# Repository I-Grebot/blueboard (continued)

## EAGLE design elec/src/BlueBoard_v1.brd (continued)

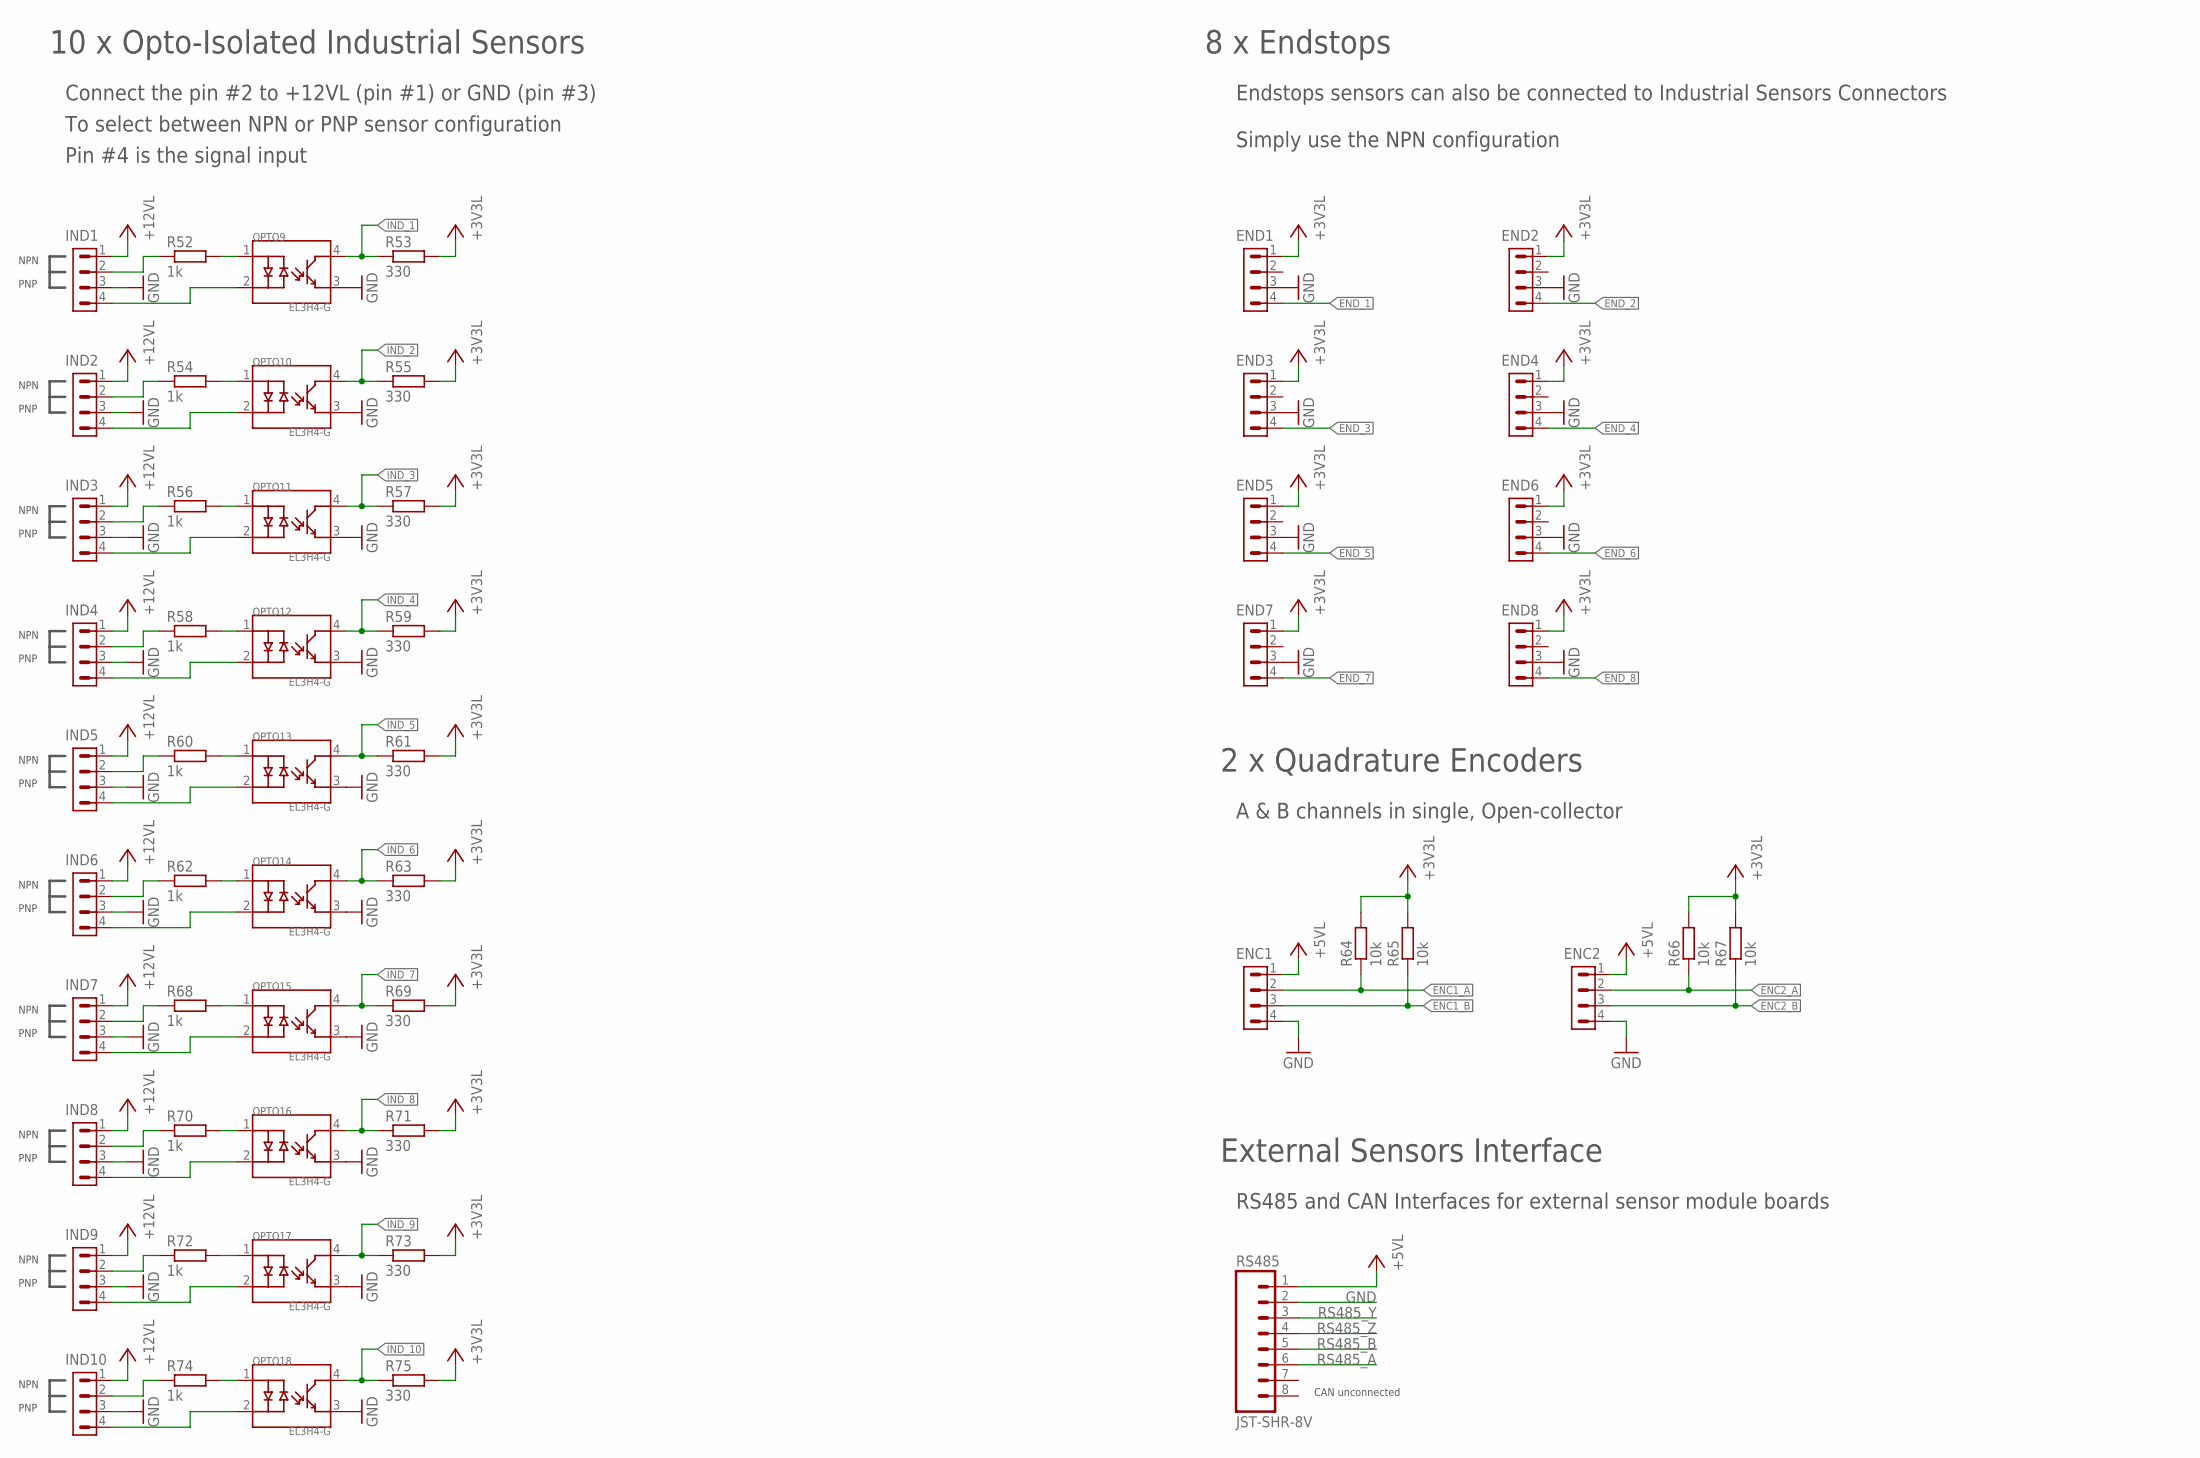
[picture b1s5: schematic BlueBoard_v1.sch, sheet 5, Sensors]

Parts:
ENC1, ENC2: CON_1.27_4
END1, END2, END3, END4, END5, END6, END7, END8: CON_1.27_4
IND1, IND2, IND3, IND4, IND5, IND6, IND7, IND8, IND9, IND10: CON_1.27_4
OPTO9, OPTO10, OPTO11, OPTO12, OPTO13, OPTO14, OPTO15, OPTO16, OPTO17, OPTO18: EL3H4-G; SSOP_4
R52, R54, R56, R58, R60, R62, R68, R70, R72, R74: 1k; R0603
R53, R55, R57, R59, R61, R63, R69, R71, R73, R75: 330; R0603
R64, R65, R66, R67: 10k; R0603
RS485: JST-SHR-8V; JST-SHR-08V

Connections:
+3V3L: END1.1, END2.1, END3.1, END4.1, END5.1, END6.1, END7.1, END8.1, R53.2, R55.2, R57.2, R59.2, R61.2, R63.2, R64.2, R65.2, R66.2, R67.2, R69.2, R71.2, R73.2, R75.2; also elsewhere on the board
+5VL: ENC1.1, ENC2.1, RS485.1; also elsewhere on the board
+12VL: IND1.1, IND2.1, IND3.1, IND4.1, IND5.1, IND6.1, IND7.1, IND8.1, IND9.1, IND10.1; also elsewhere on the board
ENC1_A: ENC1.2, R64.1; also elsewhere on the board
ENC1_B: ENC1.3, R65.1; also elsewhere on the board
ENC2_A: ENC2.2, R66.1; also elsewhere on the board
ENC2_B: ENC2.3, R67.1; also elsewhere on the board
END_1: END1.4; also elsewhere on the board
END_2: END2.4; also elsewhere on the board
END_3: END3.4; also elsewhere on the board
END_4: END4.4; also elsewhere on the board
END_5: END5.4; also elsewhere on the board
END_6: END6.4; also elsewhere on the board
END_7: END7.4; also elsewhere on the board
END_8: END8.4; also elsewhere on the board
GND: ENC1.4, ENC2.4, END1.3, END2.3, END3.3, END4.3, END5.3, END6.3, END7.3, END8.3, IND1.3, IND2.3, IND3.3, IND4.3, IND5.3, IND6.3, IND7.3, IND8.3, IND9.3, IND10.3, OPTO9.3, OPTO10.3, OPTO11.3, OPTO12.3, OPTO13.3, OPTO14.3, OPTO15.3, OPTO16.3, OPTO17.3, OPTO18.3, RS485.2; also elsewhere on the board
IND_1: OPTO9.4, R53.1; also elsewhere on the board
IND_2: OPTO10.4, R55.1; also elsewhere on the board
IND_3: OPTO11.4, R57.1; also elsewhere on the board
IND_4: OPTO12.4, R59.1; also elsewhere on the board
IND_5: OPTO13.4, R61.1; also elsewhere on the board
IND_6: OPTO14.4, R63.1; also elsewhere on the board
IND_7: OPTO15.4, R69.1; also elsewhere on the board
IND_8: OPTO16.4, R71.1; also elsewhere on the board
IND_9: OPTO17.4, R73.1; also elsewhere on the board
IND_10: OPTO18.4, R75.1; also elsewhere on the board
unnamed: IND1.2, R52.1
unnamed: OPTO9.1, R52.2
unnamed: IND1.4, OPTO9.2
unnamed: IND2.2, R54.1
unnamed: OPTO10.1, R54.2
unnamed: IND2.4, OPTO10.2
unnamed: IND3.2, R56.1
unnamed: OPTO11.1, R56.2
unnamed: IND3.4, OPTO11.2
unnamed: IND4.2, R58.1
unnamed: OPTO12.1, R58.2
unnamed: IND4.4, OPTO12.2
unnamed: IND5.2, R60.1
unnamed: OPTO13.1, R60.2
unnamed: IND5.4, OPTO13.2
unnamed: IND6.2, R62.1
unnamed: OPTO14.1, R62.2
unnamed: IND6.4, OPTO14.2
unnamed: IND7.2, R68.1
unnamed: OPTO15.1, R68.2
unnamed: IND7.4, OPTO15.2
unnamed: IND8.2, R70.1
unnamed: OPTO16.1, R70.2
unnamed: IND8.4, OPTO16.2
unnamed: IND9.2, R72.1
unnamed: OPTO17.1, R72.2
unnamed: IND9.4, OPTO17.2
unnamed: IND10.2, R74.1
unnamed: OPTO18.1, R74.2
unnamed: IND10.4, OPTO18.2
RS485_A: RS485.6; also elsewhere on the board
RS485_B: RS485.5; also elsewhere on the board
RS485_Y: RS485.3; also elsewhere on the board
RS485_Z: RS485.4; also elsewhere on the board

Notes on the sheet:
10 x Opto-Isolated Industrial Sensors
8 x Endstops
NPN
PNP
Connect the pin #2 to +12VL (pin #1) or GND (pin #3)
To select between NPN or PNP sensor configuration
Endstops sensors can also be connected to Industrial Sensors Connectors
Simply use the NPN configuration
External Sensors Interface
RS485 and CAN Interfaces for external sensor module boards
Pin #4 is the signal input
2 x Quadrature Encoders
A & B channels in single, Open-collector
CAN unconnected

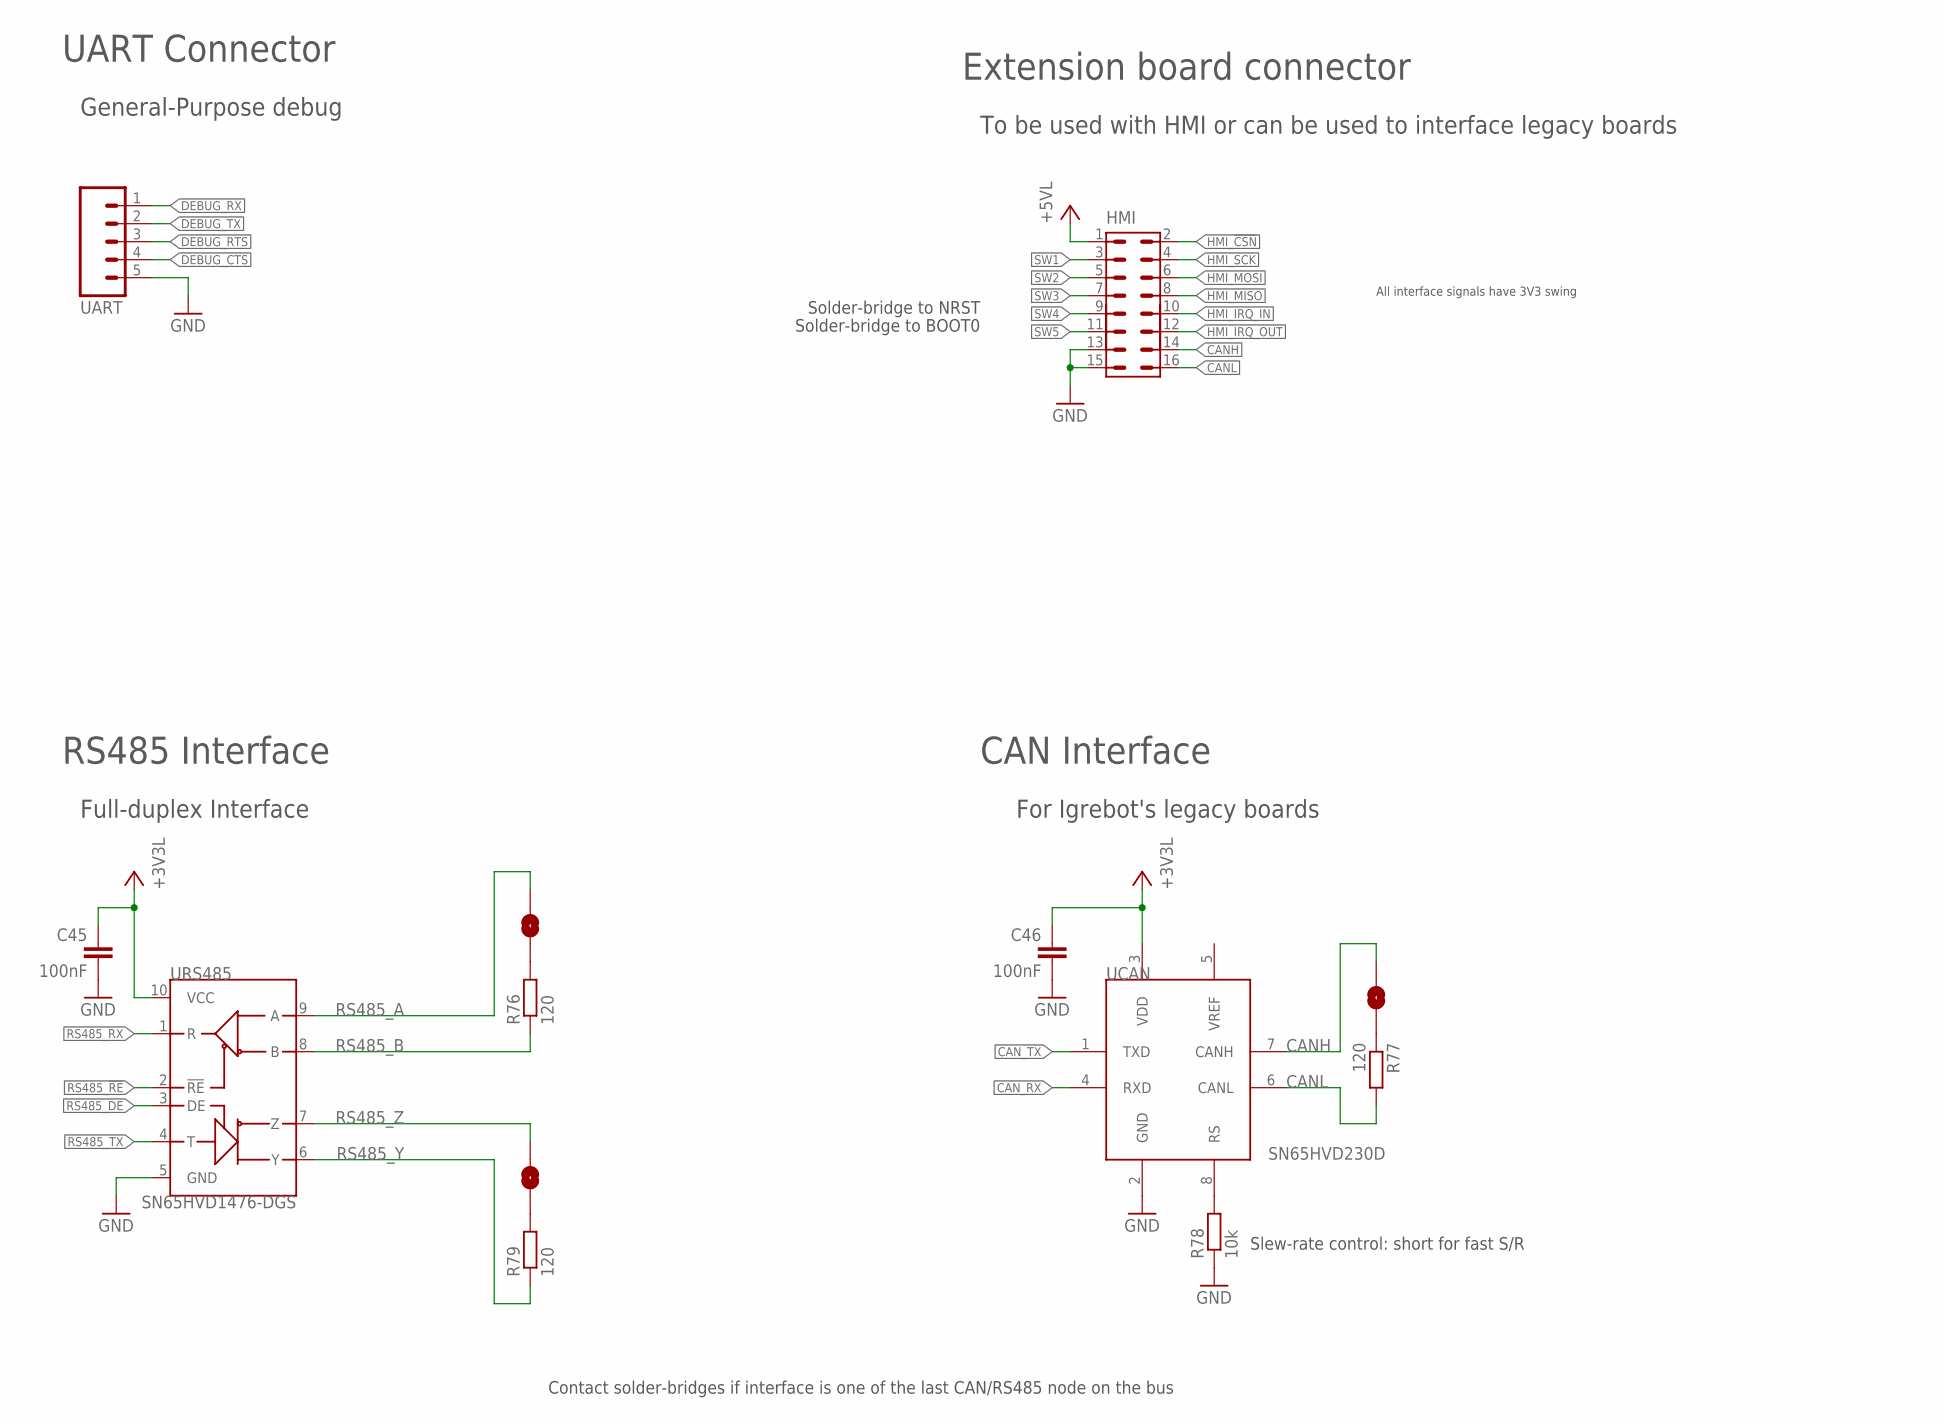
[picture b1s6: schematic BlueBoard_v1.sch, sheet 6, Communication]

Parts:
C45: 100nF; C0603K
C46: 100nF; C0603
HMI: HE10_V_16; CON_2X_2.54_V_16
R76, R77, R79: 120; R0603
R78: 10k; R0603
SJ3, SJ4, SJ5: SOLDERJUMPERNC2; SJ_2S-NOTRACE
UART: M05LOCK; 1X05_LOCK
UCAN: SN65HVD230D; SO-08
URS485: SN65HVD1476-DGS; MSOP-10

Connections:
+3V3L: C45.1, C46.1, UCAN.3 (VDD), URS485.10 (VCC); also elsewhere on the board
+5VL: HMI.1; also elsewhere on the board
CANH: HMI.14, SJ4.1, UCAN.7 (CANH)
CANL: HMI.16, R77.2, UCAN.6 (CANL)
CAN_RX: UCAN.4 (RXD); also elsewhere on the board
CAN_TX: UCAN.1 (TXD); also elsewhere on the board
DEBUG_CTS: UART.4; also elsewhere on the board
DEBUG_RTS: UART.3; also elsewhere on the board
DEBUG_RX: UART.1; also elsewhere on the board
DEBUG_TX: UART.2; also elsewhere on the board
GND: C45.2, C46.2, HMI.13, HMI.15, R78.1, UART.5, UCAN.2 (GND), URS485.5 (GND); also elsewhere on the board
HMI_!CSN!: HMI.2; also elsewhere on the board
HMI_IRQ_IN: HMI.10; also elsewhere on the board
HMI_IRQ_OUT: HMI.12; also elsewhere on the board
HMI_MISO: HMI.8; also elsewhere on the board
HMI_MOSI: HMI.6; also elsewhere on the board
HMI_SCK: HMI.4; also elsewhere on the board
unnamed: R78.2, UCAN.8 (RS)
unnamed: R77.1, SJ4.2
unnamed: R76.2, SJ3.2
unnamed: R79.2, SJ5.2
RS485_!RE!: URS485.2 (!RE!); also elsewhere on the board
RS485_A: SJ3.1, URS485.9 (A); also elsewhere on the board
RS485_B: R76.1, URS485.8 (B); also elsewhere on the board
RS485_DE: URS485.3 (DE); also elsewhere on the board
RS485_RX: URS485.1 (R); also elsewhere on the board
RS485_TX: URS485.4 (T); also elsewhere on the board
RS485_Y: R79.1, URS485.6 (Y); also elsewhere on the board
RS485_Z: SJ5.1, URS485.7 (Z); also elsewhere on the board
SW1: HMI.3; also elsewhere on the board
SW2: HMI.5; also elsewhere on the board
SW3: HMI.7; also elsewhere on the board
SW4: HMI.9; also elsewhere on the board
SW5: HMI.11; also elsewhere on the board

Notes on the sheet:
UART Connector
For Igrebot's legacy boards
CAN Interface
Contact solder-bridges if interface is one of the last CAN/RS485 node on the bus
RS485 Interface
Full-duplex Interface
To be used with HMI or can be used to interface legacy boards
Extension board connector
All interface signals have 3V3 swing
Solder-bridge to NRST
Solder-bridge to BOOT0
Slew-rate control: short for fast S/R
General-Purpose debug

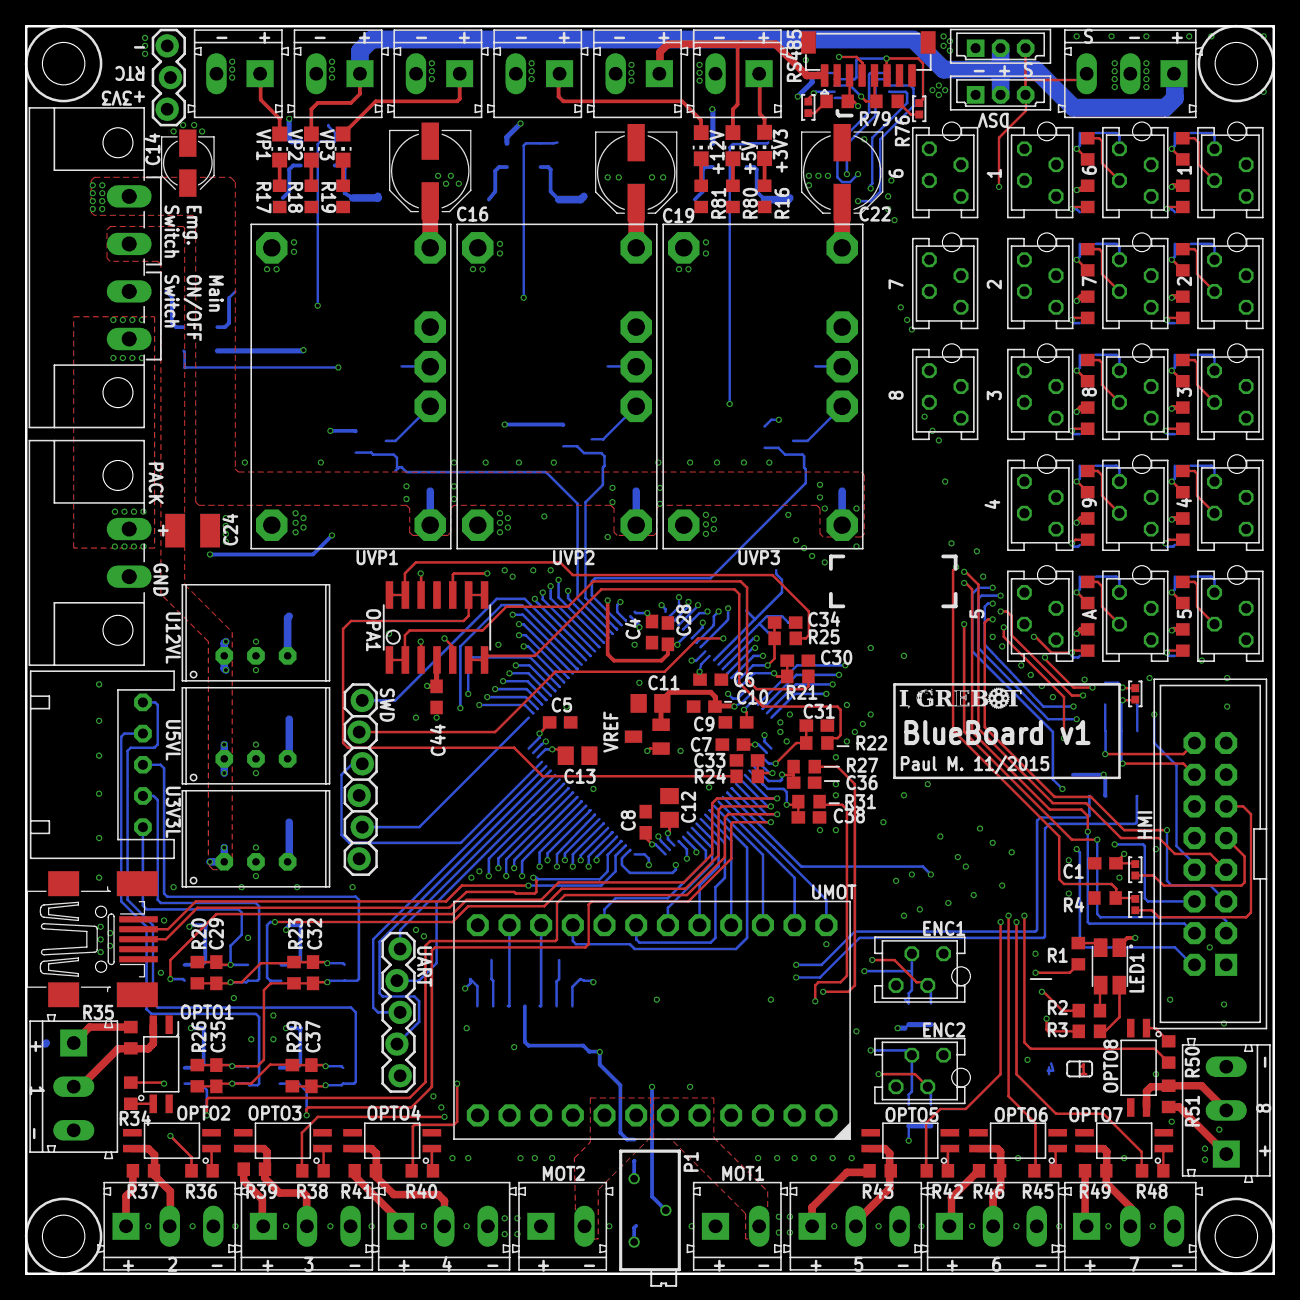
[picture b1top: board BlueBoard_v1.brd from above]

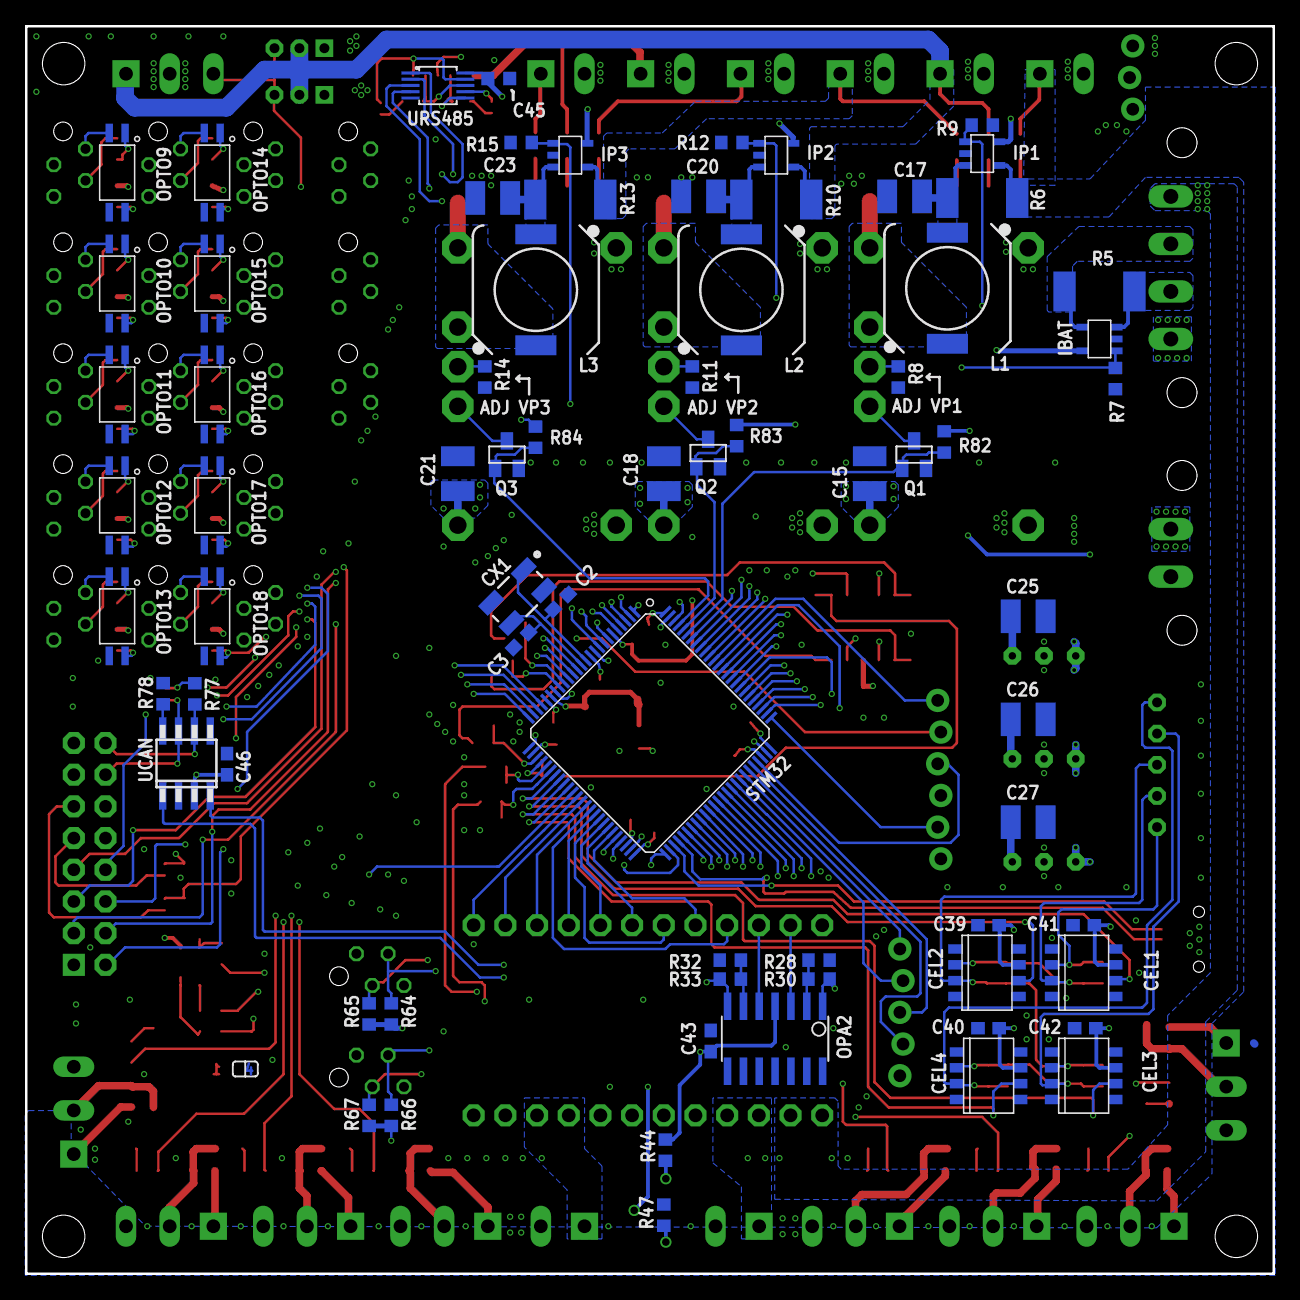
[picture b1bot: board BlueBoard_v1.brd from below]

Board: 4 copper layers, 100.0 x 100.0 mm, 239 parts (73 on the bottom side), 204 nets.

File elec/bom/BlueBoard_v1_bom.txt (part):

Partlist exported from C:/Users/Paul/Documents/Work/Igrebot/SVN/trunk/Elec/2016/BlueBoard v1/src/BlueBoard_v1.sch at 01/11/2015 20:36:05

Assembly variant: 

Part         Value                  Device                 Package                Description                                       
ASV1         CON_3.5_3              CON_3.5_3              CON_3.5_3                                                                
ASV2         CON_3.5_3              CON_3.5_3              CON_3.5_3                                                                
ASV3         CON_3.5_3              CON_3.5_3              CON_3.5_3                                                                
ASV4         CON_3.5_3              CON_3.5_3              CON_3.5_3                                                                
ASV5         CON_3.5_3              CON_3.5_3              CON_3.5_3                                                                
ASV6         CON_3.5_3              CON_3.5_3              CON_3.5_3                                                                
ASV7         CON_3.5_3              CON_3.5_3              CON_3.5_3                                                                
ASV8         CON_3.5_3              CON_3.5_3              CON_3.5_3                                                                
BAT1         MC15-GF-3.81-LR_2      MC15-GF-3.81-LR_2      CON_3.81_LR_2                                                            
BAT2         JST-XH-S_5             JST-XH-S_5             JST-XH-5S                                                                
C1           100nF                  C-EUC0603              C0603                  CAPACITOR, European symbol                        
C2           18 pF                  C-EUC0603              C0603                  CAPACITOR, European symbol                        
C3           18 pF                  C-EUC0603              C0603                  CAPACITOR, European symbol                        
C4           100nF                  C-EUC0603              C0603                  CAPACITOR, European symbol                        
C5           100nF                  C-EUC0603              C0603                  CAPACITOR, European symbol                        
C6           100nF                  C-EUC0603              C0603                  CAPACITOR, European symbol                        
C7           100nF                  C-EUC0603              C0603                  CAPACITOR, European symbol                        
C8           100nF                  C-EUC0603              C0603                  CAPACITOR, European symbol                        
C9           10nF                   C-EUC0603              C0603                  CAPACITOR, European symbol                        
C10          10nF                   C-EUC0603              C0603                  CAPACITOR, European symbol                        
C11          1uF                    C-EUC0805              C0805                  CAPACITOR, European symbol                        
C12          2.2uF                  C-EUC0805              C0805                  CAPACITOR, European symbol                        
C13          2.2uF                  C-EUC0805              C0805                  CAPACITOR, European symbol                        
C14          470uF                  CPOL-EUB               PANASONIC_B            POLARIZED CAPACITOR, European symbol              
C15          22uF                   C-EUC3225              C3225                  CAPACITOR, European symbol                        
C16          470uF                  CPOL-EUD               PANASONIC_D            POLARIZED CAPACITOR, European symbol              
C17          1uF                    C-EUC3225              C3225                  CAPACITOR, European symbol                        
C18          22uF                   C-EUC3225              C3225                  CAPACITOR, European symbol                        
C19          470uF                  CPOL-EUD               PANASONIC_D            POLARIZED CAPACITOR, European symbol              
C20          1uF                    C-EUC3225              C3225                  CAPACITOR, European symbol                        
C21          22uF                   C-EUC3225              C3225                  CAPACITOR, European symbol                        
C22          470uF                  CPOL-EUD               PANASONIC_D            POLARIZED CAPACITOR, European symbol              
C23          1uF                    C-EUC3225              C3225                  CAPACITOR, European symbol                        
C24          22uF                   C-EUC3225              C3225                  CAPACITOR, European symbol                        
C25          47uF                   C-EUC1210              C1210                  CAPACITOR, European symbol                        
C26          47uF                   C-EUC1210              C1210                  CAPACITOR, European symbol                        
C27          47uF                   C-EUC1210              C1210                  CAPACITOR, European symbol                        
C28          100nF                  C-EUC0603              C0603                  CAPACITOR, European symbol                        
C29          100nF                  C-EUC0603              C0603                  CAPACITOR, European symbol                        
C30          3.3nF                  C-EUC0603              C0603                  CAPACITOR, European symbol                        
C31          3.3nF                  C-EUC0603              C0603                  CAPACITOR, European symbol                        
C32          100nF                  C-EUC0603              C0603                  CAPACITOR, European symbol                        
C33          3.3nF                  C-EUC0603              C0603                  CAPACITOR, European symbol                        
C34          3.3nF                  C-EUC0603              C0603                  CAPACITOR, European symbol                        
C35          100nF                  C-EUC0603              C0603                  CAPACITOR, European symbol                        
C36          3.3nF                  C-EUC0603              C0603                  CAPACITOR, European symbol                        
C37          100nF                  C-EUC0603              C0603                  CAPACITOR, European symbol                        
C38          3.3nF                  C-EUC0603              C0603                  CAPACITOR, European symbol                        
C39          220nF                  C-EUC0603              C0603                  CAPACITOR, European symbol                        
C40          220nF                  C-EUC0603              C0603                  CAPACITOR, European symbol                        
C41          220nF                  C-EUC0603              C0603                  CAPACITOR, European symbol                        
C42          220nF                  C-EUC0603              C0603                  CAPACITOR, European symbol                        
C43          100nF                  C-EUC0603              C0603                  CAPACITOR, European symbol                        
C44          100nF                  C-EUC0603              C0603                  CAPACITOR, European symbol                        
C45          100 nF                 C-EUC0603K             C0603K                 CAPACITOR, European symbol                        
C46          100nF                  C-EUC0603              C0603                  CAPACITOR, European symbol                        
CEL1         LT1990                 LT1990                 S8                                                                       
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
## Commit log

2016-11-09 Migration from SVN: added all files from 2016:T1:robot1
2016-11-09 Updated .gitignore to also ignore building directories /Debug/ and /Release/
2016-11-10 Testing travis-ci integration
2016-11-10 Testing travis-ci yaml
2016-11-10 Cleaned up travis
2016-12-04 Fixed incorrect UART definition for 9b word-length mode. Added bootloader batch script.
2016-12-04 Migration to FreeRTOS v9.0.0. Added FreeRTOS-Plus CLI.
2016-12-04 Added a Shell using FreeRTOS + CLI. Implemented some basic demo functions -- need to be largely extended to reach its full usefulness.
2016-12-25 Skeleton of shell functions. Started implementation of variable set/get system -- WIP
2017-01-01 Shell fully functionnal
    Debug (Serial) Interface fully managed with interrupts & Queues.
    Still some work todo with the CLI and the PROBE function
2017-01-05 Setup new variable structure for the shell
2017-01-08 Added shell probe function
2017-01-10 Filled-up variables definition with most motion stuff
2017-01-21 Updated .gitignore
2017-01-21 Merged firm_blueboard and elec_blueboard into 1 repository
2017-01-23 Reorganization & cleanup
2017-01-30 Massive reorganization, split BlueBoard hardware into dedicated BSP - WIP
2017-01-30 Reorg followup
2017-02-04 BSP Cleanup complete
2017-02-10 Firmware main project reorg
2017-02-10 Worked on dynamixel component
2017-02-11 Basic shell Digital Servo Command function
2017-02-15 Worked on DXL lib. All DXL_V1 hardware handlers done.
2017-02-16 DXL Lib with multi interfaces & multi protocol - WIP
2017-03-19 DXL Lib WIP
2017-03-20 Working DXL V1 return status / receive packet
2017-03-21 DXL Lib: working read function
2017-03-30 Clean DSV shell commands
2017-04-09 Finally fixed the f* problem with printf float
2017-04-15 Added support for GUI management of DXL. Added Shell dump function
2017-04-16 DXL: Started to integrate V2 com functions
2017-04-17 DXL Lib: finished integration of COM V2 ; still few details TBD
2017-04-18 Fixed errors in the dsv shell command and dxl registers module
2017-04-20 Cleanup motion module, added some debug features
2017-04-22 Monitoring module in place (still some debug todo)
2017-04-23 Reorganization of the motion & strategy code.
2017-04-23 Basic bare-bone strategy + AI + task system -- missing high level mgmt
2017-04-24 Strategy cleanup
2017-04-25 OS Tasks notification system
2017-04-25 Implemented debug strategy software notifiers through shell commands
2017-04-26 Small reorganization of "strategy" (now sequencer). First version of ai_manage -- WIP
2017-04-26 Worked on Sequencer + AI + Tasks
2017-04-29 Added beacons SPI doc
2017-05-02 Added beacons module
2017-05-03 Updated sequencer & tasks memory mgmt
2017-05-03 BOM with 2017 re-order
2017-05-04 Simplification of AI's IDLE task (now = NULL)
2017-05-05 Added most of physicals + PF obstacles
2017-05-06 Physics update, temporary printing func for tests
2017-05-07 Updated some physics constant and sequencer commands
2017-05-17 Demo homolog' program ready (untested)
2017-05-17 Fixed wp coordinate with color
2017-05-17 Same with exit_start poi
2017-05-19 Unit testing @Persycup 2017
    Start sequence bypassed, physical paramters updated, few waypoints pushing modules.
2017-05-19 Basic working SPI hardware for beacons
2017-05-20 Added system:modules -- WIP
2017-05-20 2017_T1_R1: Auto stash before merge of "2017_T1_R1" and "origin/2017_T1_R1"
2017-05-20 Modules sub-system operational for tests
2017-05-21 Adjusted AVS control constants
2017-05-21 Fixed stack overflow of AI task when receiving notification
2017-05-22 Fixed some important AVD errors, updated ai, tasks and feedbacks to GUI
2017-05-23 Mostly worked on AI + PF
2017-05-26 Fixed DXL incorrect register mapping
2017-05-27 Modified code after Match #4
2017-05-28 Code after match 5
2018-02-06 Fresh start for 2018
    Environment description ok
    Sequencer started, robot is control (no move)
    Merge branch '2018_T1_R1' into origin/2018_T1_R1
2018-02-07 go to home automation switch
    creation of the ai task
    shut the avoidance
2018-04-24 Trigger automatique switch
    Including submodule self test and avoidance management
2018-05-01 Strategie after Vercors Sciences
    Switch + bee + cubes + our water distributor
2018-05-04 Save before 2nd table tests session
    Add index, Add servo Iface itf, correct stall and color management
2018-05-06 Strategy after 2nd tests session at Vercors Sciences
    Arms adaptation, color bug correction, add shooter (the ugly way), add new waypoints for 2nd water recuperator
2018-05-07 Bugs corrections
    Automatic angle color correction, split program in 5tasks, use abs coord only
2018-05-10 1rst match
    5 tasks, switch, bee, openner, shooter misoperating : avd ok
2018-05-10 2nd match garbage
2018-05-10 Motion control setted-up
2018-05-10 After table test (need adjustments)
2018-05-10 Adjustment
2018-05-10 Add thumb XL320 management
2018-05-11 3rd match program strategy
2018-05-11 4th match
2018-05-11 Blocking correction
2018-05-12 5th match
2018-05-12 small adjustment before 5th match
2018-05-16 Speed modification before Persycup
2018-05-16 1er match persycup
2018-05-16 3ème match Persycup
